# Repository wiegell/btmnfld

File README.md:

# WIP

4x6 mod of Btrfld

# Btmnfld

Pronounced "batmanfold".
Much credit to original creator Solidhal: https://github.com/SolidHal/btrfld

## Features common to original btrfld
- 5 key dactyl-manuform-mini thumb cluster
- flat, tented qwerty keys
- folds flat for portability

## Alterations from original btrfld
- Main body has an extra colum (pseudo 4x6)
- Less tenting (22 deg vs. 32 in original)
- No wireless - Elite C for MCU (wiring usb directly to pcb)
- Somewhat hidden wiring under the "bat"
- Using threaded 3mm steel rod instead of smooth (fixed with washers and nuts)
- Magnetic latches for keeping the board folded

## Parts:

- USB C breakout basic breakout board 
  - Used this one https://let-elektronik.dk/shop/950-stik-breakout/15100--usb-c-breakout/

- choc v1 keyswitches

- diodes

- 3mm diameter threaded steel rod

- 1.27mm flat ribbon cable

- 1x Elite C
  
- 3d printed pieces, located in the STLs folder

- 50x1 mm circular magnetic bottom plate (optional)
  - I used one i had lying around: https://thestick.company/product/imsticker/ (the medium size)

- Four 6x4x2 mm neodymium magnets

- One circular 4x1 mm neodymium magnet

- Glue for magnets (mostly held by 3d structure)

## Modifying
Edit `btmnfld.FCStd` using FreeCad.
I am by no means a FreeCad expert, so I'm sure its built suboptimally.
Expect slow working with the files bc. of the many crude edits.
Should anyone want to do alterations i would advice simply "building on top" instead of going back the chain of events to prevent having to remap all skethces and external geometry (i did that and it took forever...). See https://wiki.freecadweb.org/Topological_naming_problem

## Print Settings:
```
Supports on buildplate
Detect Bridging
100% infill
0.20mm
PLA/PETG
```

## Assembly Tips:

- Must trim a very very slight amount off of the center pin on keyswitches over the body/thumbcluster rod
  - switch above this must be rotated to give clearance for the rod locker

- Thumb cluster end of rod gets glued in place

- Reference the images in the "BuildPictures" folder

## Future development
- Underglow?

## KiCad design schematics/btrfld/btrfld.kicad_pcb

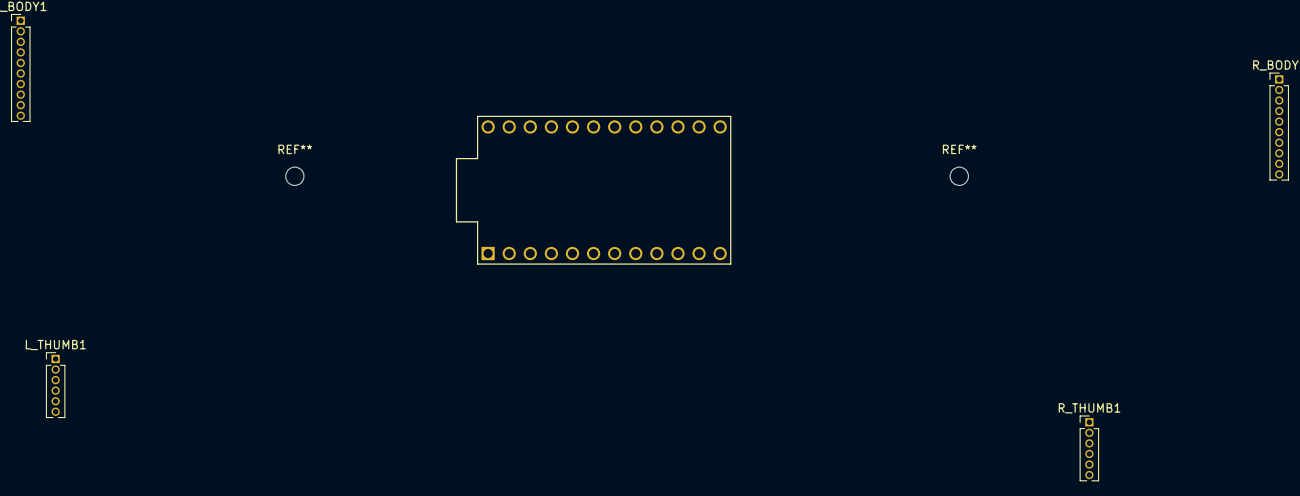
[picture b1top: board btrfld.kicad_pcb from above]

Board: 2 copper layers, 5 parts (0 on the bottom side), 17 nets, no tracks yet.

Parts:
L_BODY1: Conn_01x10; PinHeader_1x10_P1.27mm_Vertical
L_THUMB1: Conn_01x06; PinHeader_1x06_P1.27mm_Vertical
PRO_MICRO1: Conn_02x12_Top_Bottom; ProMicro-EnforcedTop
R_BODY1: Conn_01x10; PinHeader_1x10_P1.27mm_Vertical
R_THUMB1: Conn_01x06; PinHeader_1x06_P1.27mm_Vertical

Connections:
/B1: PRO_MICRO1.21, R_BODY1.8, R_THUMB1.4
/B2: PRO_MICRO1.23, R_BODY1.6, R_THUMB1.2
/B3: PRO_MICRO1.22, R_BODY1.7, R_THUMB1.3
/B4: L_BODY1.9, L_THUMB1.5, PRO_MICRO1.11
/B5: L_BODY1.10, PRO_MICRO1.12
/B6: PRO_MICRO1.24, R_BODY1.5, R_THUMB1.1
/C6: L_BODY1.6, L_THUMB1.2, PRO_MICRO1.8
/D0: L_BODY1.4, PRO_MICRO1.6, R_BODY1.4
/D1: L_BODY1.3, PRO_MICRO1.5, R_BODY1.3
/D2: L_BODY1.2, PRO_MICRO1.2, R_BODY1.2
/D3: L_BODY1.1, PRO_MICRO1.1, R_BODY1.1
/D4: L_BODY1.5, L_THUMB1.1, PRO_MICRO1.7
/D7: L_BODY1.7, L_THUMB1.3, PRO_MICRO1.9
/E6: L_BODY1.8, L_THUMB1.4, PRO_MICRO1.10
/F5: L_THUMB1.6, PRO_MICRO1.18, R_THUMB1.6
/F6: PRO_MICRO1.19, R_BODY1.10
/F7: PRO_MICRO1.20, R_BODY1.9, R_THUMB1.5

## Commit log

2022-06-16 updated exports
2022-06-16 cleanup
2022-06-16 supports ok, but wrong overall angle
2022-06-16 ok angle
2022-06-28 new pocket for pro micro and small adjustments
2022-07-12 start kicad
2022-07-13 major rerouting of cables and swap to elite c
2022-07-13 larger wire space
2022-07-13 batman art
2022-07-14 batman art2
2022-07-14 batman art final
2022-07-14 magnet slots
2022-07-15 more magnets
2022-07-15 readme and stls exports
2022-07-15 more readme changes
2022-07-23 new pocket size for elite c
2022-07-24 larger magnet pockets
2022-07-24 usb submerged
2022-07-24 thumb support and small adjustments
2022-07-25 most changes done for next print of baseplate
